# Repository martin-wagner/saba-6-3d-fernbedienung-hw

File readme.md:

### Saba Webradio

Das Saba Webradio erweitert ein Saba Automatic Radio um die folgenden Funktionen:
- W-Lan Webradio
- Steuerung von Automatik und Lautst"arke per Webinterface, MQTT, IR Fernbedienung ...
- Steuerung des Webradio per Radio Automatiktasten

Es kann direkt auf die Anschlussbuchse für die Fernbedienung aufgesteckt werden. Kompatibel sind mind. das Meersburg und Freiburg 6-3D. Am Gerät selbst sind keine Modifikationen notwendig (aber empfehlen). Der Audioausgang des Webradio wird mit dem TA Eingang des Radios verbunden und kann durch Wahl des zugehörigen Eingangs am Radio verwendet werden.

Das Webradio basiert auf dem [ESP32-Radio Projekt von Ed Smallenburg](https://github.com/Edzelf/ESP32-Radio).

[Hardware](https://github.com/martin-wagner/saba-6-3d-fernbedienung-hw)

[Software](https://github.com/martin-wagner/ESP32-Radio)

[Doku](doku/latex/doku.pdf)

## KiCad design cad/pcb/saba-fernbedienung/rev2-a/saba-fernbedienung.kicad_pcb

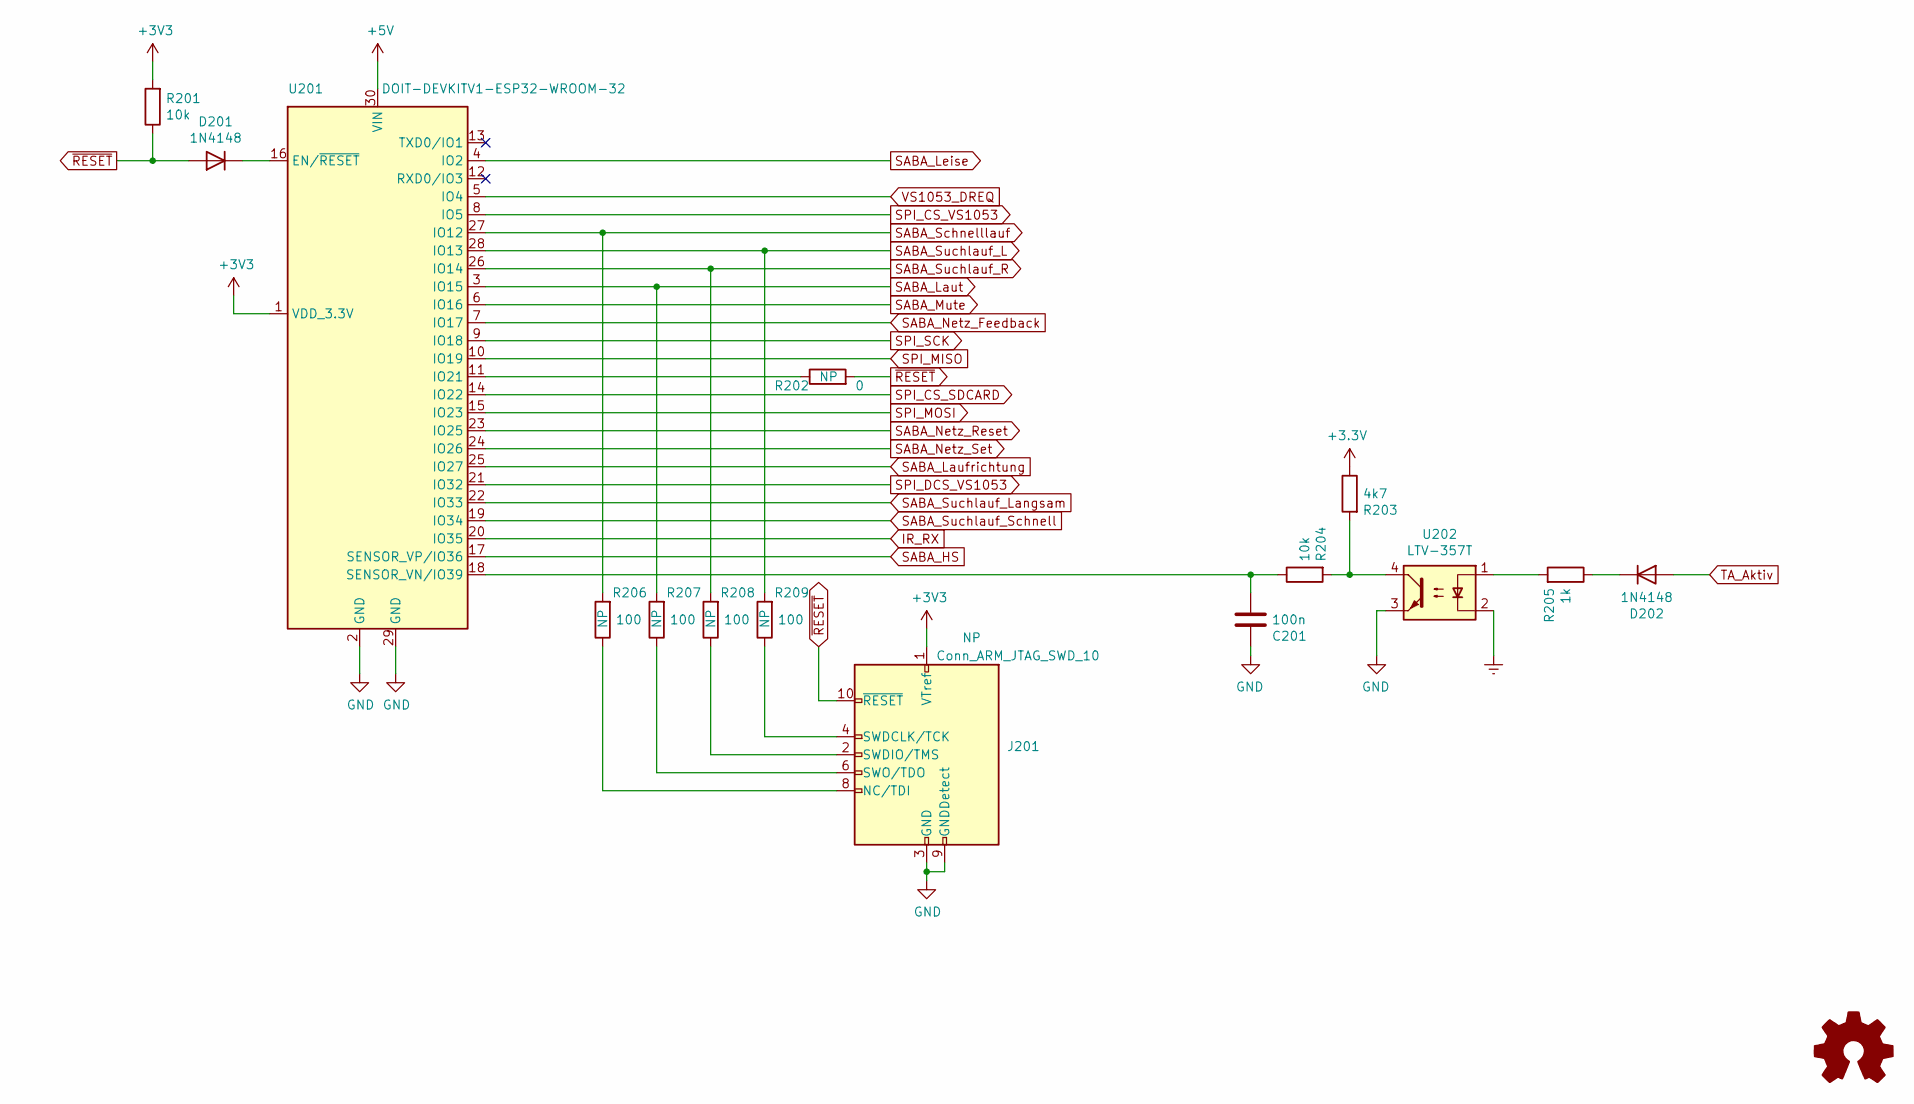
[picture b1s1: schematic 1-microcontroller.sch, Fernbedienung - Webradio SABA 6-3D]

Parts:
C201: 100n; C_0603_1608Metric
D201, D202: 1N4148; D_SOD-323F
J201: Conn_ARM_JTAG_SWD_10; PinHeader_2x05_P1.27mm_Vertical
R201, R204: 10k; R_0603_1608Metric
R202: 0; R_0603_1608Metric
R203: 4k7; R_0603_1608Metric
R205: 1k; R_0603_1608Metric
R206, R207, R208, R209: 100; R_0603_1608Metric
U201: DOIT-DEVKITV1-ESP32-WROOM-32
U202: LTV-357T; SO-4_4.4x3.6mm_P2.54mm

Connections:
+5V: U201.30 (VIN); also elsewhere on the board
Earth: U202.2; also elsewhere on the board
GND: C201.1, J201.3 (GND), J201.5 (GND), J201.9 (GNDDetect), U201.2 (GND), U201.29 (GND), U202.3; also elsewhere on the board
IR_RX: U201.20 (IO35); also elsewhere on the board
unnamed: C201.2, R204.1, U201.18 (SENSOR_VN/IO39)
unnamed: D201.1 (K), U201.16 (EN/~RESET)
unnamed: D202.1 (K), R205.1
unnamed: J201.2 (SWDIO/TMS), R208.1
unnamed: J201.4 (SWDCLK/TCK), R209.1
unnamed: J201.6 (SWO/TDO), R207.1
unnamed: J201.8 (NC/TDI), R206.1
unnamed: R202.1, U201.11 (IO21)
unnamed: R203.2, R204.2, U202.4
unnamed: R205.2, U202.1
SABA_HS: U201.17 (SENSOR_VP/IO36); also elsewhere on the board
SABA_Laufrichtung: U201.25 (IO27); also elsewhere on the board
SABA_Laut: R207.2, U201.3 (IO15); also elsewhere on the board
SABA_Leise: U201.4 (IO2); also elsewhere on the board
SABA_Mute: U201.6 (IO16); also elsewhere on the board
SABA_Netz_Feedback: U201.7 (IO17); also elsewhere on the board
SABA_Netz_Reset: U201.23 (IO25); also elsewhere on the board
SABA_Netz_Set: U201.24 (IO26); also elsewhere on the board
SABA_Schnelllauf: R206.2, U201.27 (IO12); also elsewhere on the board
SABA_Suchlauf_L: R209.2, U201.28 (IO13); also elsewhere on the board
SABA_Suchlauf_Langsam: U201.22 (IO33); also elsewhere on the board
SABA_Suchlauf_R: R208.2, U201.26 (IO14); also elsewhere on the board
SABA_Suchlauf_Schnell: U201.19 (IO34); also elsewhere on the board
SPI_CS_SDCARD: U201.14 (IO22); also elsewhere on the board
SPI_CS_VS1053: U201.8 (IO5); also elsewhere on the board
SPI_DCS_VS1053: U201.21 (IO32); also elsewhere on the board
SPI_MISO: U201.10 (IO19); also elsewhere on the board
SPI_MOSI: U201.15 (IO23); also elsewhere on the board
SPI_SCK: U201.9 (IO18); also elsewhere on the board
TA_Aktiv: D202.2 (A); also elsewhere on the board
VS1053_DREQ: U201.5 (IO4); also elsewhere on the board
~RESET: D201.2 (A), J201.10 (~RESET~), R201.1, R202.2; also elsewhere on the board

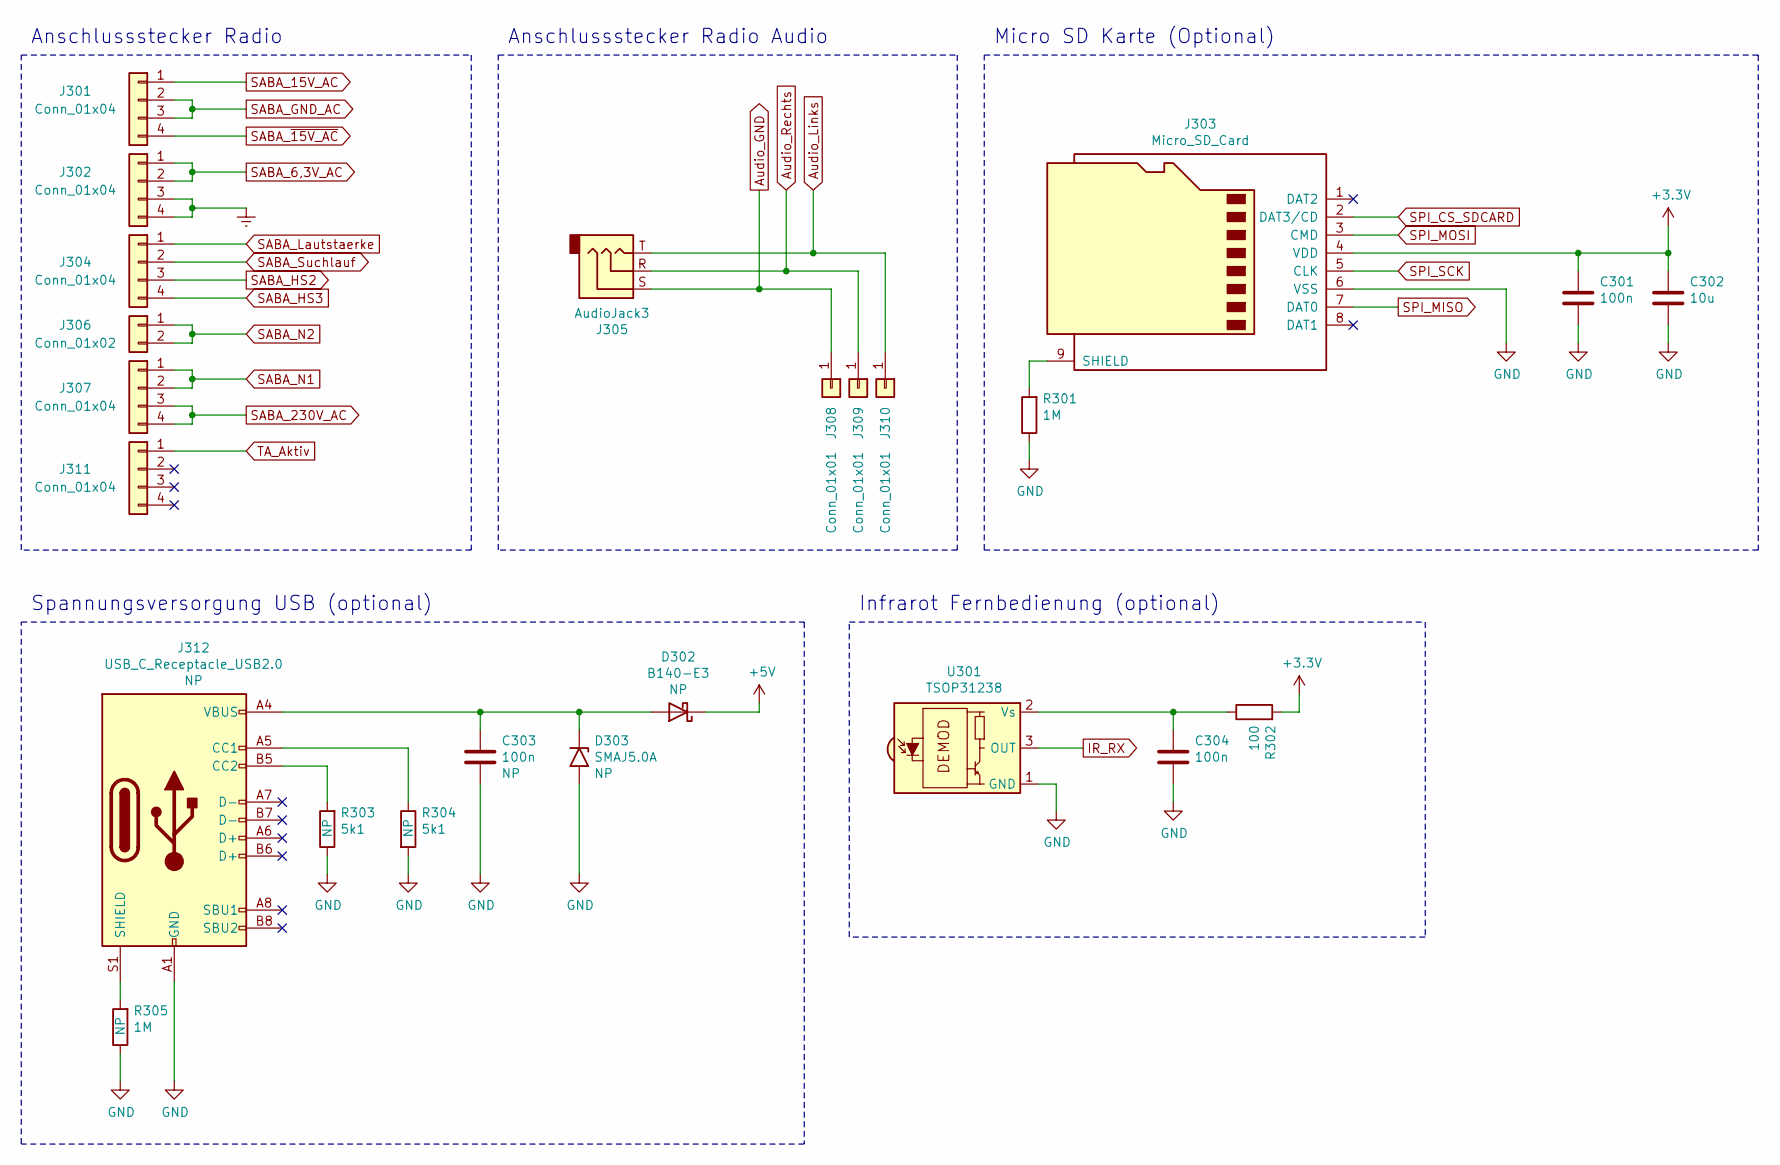
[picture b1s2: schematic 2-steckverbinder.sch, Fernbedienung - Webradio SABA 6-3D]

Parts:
C301, C303, C304: 100n; C_0603_1608Metric
C302: 10u; C_1206_3216Metric
D302: B140-E3; D_SMA
D303: SMAJ5.0A; D_SMA
J301, J302, J304, J307, J311: Conn_01x04; PinHeader_1x04_P2.54mm_Vertical
J303: Micro_SD_Card; microSD_HC_Hirose_DM3AT-SF-PEJM5
J305: AudioJack3; Jack_3.5mm_CUI_SJ-3523-SMT_Horizontal
J306: Conn_01x02; PinHeader_1x02_P2.54mm_Vertical
J308, J309, J310: Conn_01x01; PinHeader_1x01_P2.54mm_Vertical
J312: USB_C_Receptacle_USB2.0; USB_C_Receptacle_HRO_TYPE-C-31-M-12
R301, R305: 1M; R_0603_1608Metric
R302: 100; R_0603_1608Metric
R303, R304: 5k1; R_0603_1608Metric
U301: TSOP31238; Vishay_CAST-3Pin

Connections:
+5V: D302.1 (K); also elsewhere on the board
Audio_GND: J305.S, J308.1; also elsewhere on the board
Audio_Links: J305.T, J310.1; also elsewhere on the board
Audio_Rechts: J305.R, J309.1; also elsewhere on the board
Earth: J302.3, J302.4; also elsewhere on the board
GND: C301.2, C302.2, C303.2, C304.2, D303.2 (A2), J303.6 (VSS), J312.A1 (GND), J312.A12 (GND), J312.B1 (GND), J312.B12 (GND), R301.1, R303.1, R304.2, R305.1, U301.1 (GND); also elsewhere on the board
IR_RX: U301.3 (OUT); also elsewhere on the board
unnamed: C303.1, D302.2 (A), D303.1 (A1), J312.A4 (VBUS), J312.A9 (VBUS), J312.B4 (VBUS), J312.B9 (VBUS)
unnamed: C304.1, R302.1, U301.2 (Vs)
unnamed: J303.9 (SHIELD), R301.2
unnamed: J312.A5 (CC1), R304.1
unnamed: J312.B5 (CC2), R303.2
unnamed: J312.S1 (SHIELD), R305.2
SABA_6,3V_AC: J302.1, J302.2; also elsewhere on the board
SABA_15V_AC: J301.1; also elsewhere on the board
SABA_230V_AC: J307.3, J307.4; also elsewhere on the board
SABA_GND_AC: J301.2, J301.3; also elsewhere on the board
SABA_HS2: J304.3; also elsewhere on the board
SABA_HS3: J304.4; also elsewhere on the board
SABA_Lautstaerke: J304.1; also elsewhere on the board
SABA_N1: J307.1, J307.2; also elsewhere on the board
SABA_N2: J306.1, J306.2; also elsewhere on the board
SABA_Suchlauf: J304.2; also elsewhere on the board
SABA_~15V_AC: J301.4; also elsewhere on the board
SPI_CS_SDCARD: J303.2 (DAT3/CD); also elsewhere on the board
SPI_MISO: J303.7 (DAT0); also elsewhere on the board
SPI_MOSI: J303.3 (CMD); also elsewhere on the board
SPI_SCK: J303.5 (CLK); also elsewhere on the board
TA_Aktiv: J311.1; also elsewhere on the board

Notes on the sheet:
Anschlussstecker Radio
Spannungsversorgung USB (optional)
Micro SD Karte (Optional)
Infrarot Fernbedienung (optional)
Anschlussstecker Radio Audio

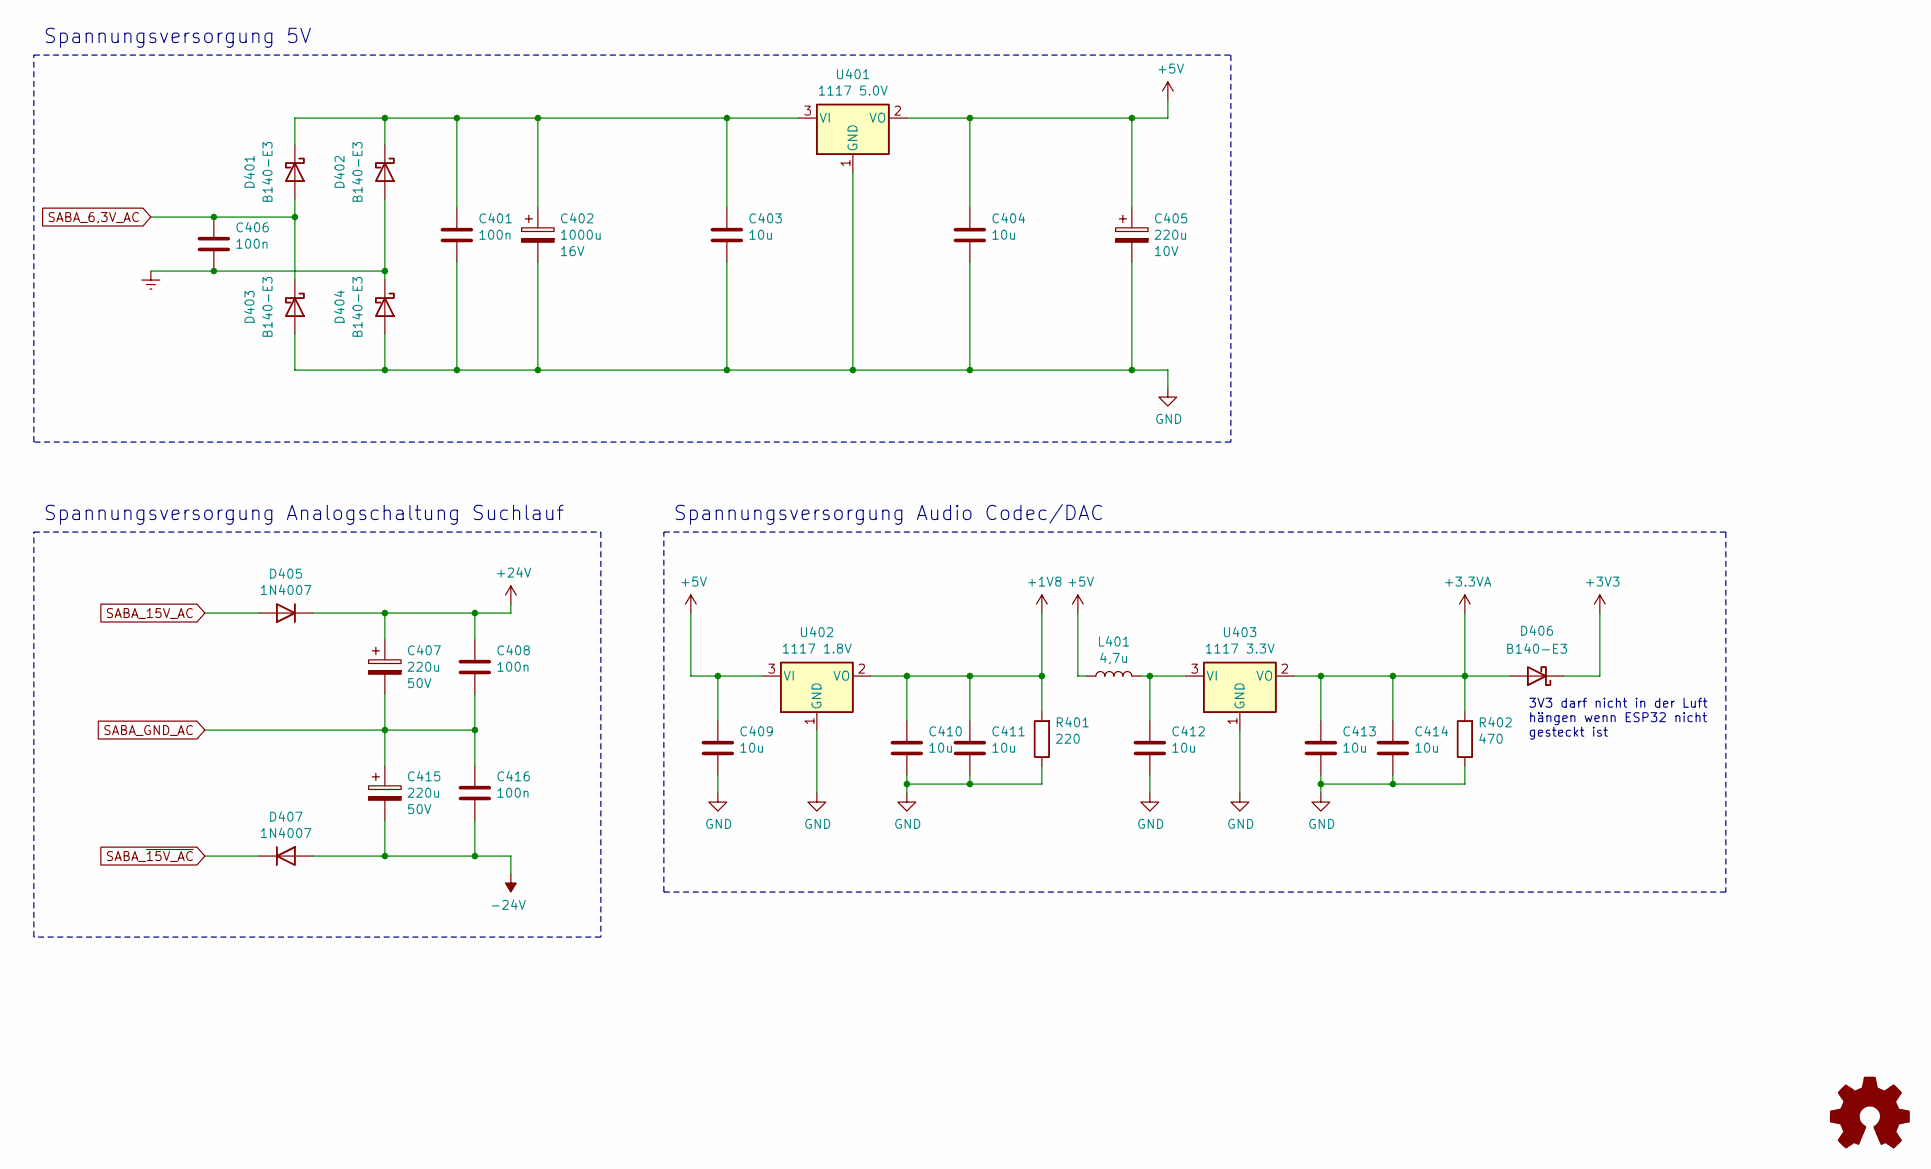
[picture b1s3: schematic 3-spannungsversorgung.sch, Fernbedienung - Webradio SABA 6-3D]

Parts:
C401, C406, C408, C416: 100n; C_0603_1608Metric
C402: 1000u; CP_Radial_D10.0mm_P5.00mm_L20.00mm_liegend; Voltage 16V
C403, C404, C409, C410, C411, C412, C413, C414: 10u; C_1206_3216Metric
C405: 220u; CP_Radial_D10.0mm_P5.00mm_L12.50mm_liegend; Voltage 10V
C407, C415: 220u; CP_Radial_D10.0mm_P5.00mm; Voltage 50V
D401, D402, D403, D404, D406: B140-E3; D_SMA
D405, D407: 1N4007; D_SMA
L401: 4,7u; WE-LQ
R401: 220; R_0603_1608Metric
R402: 470; R_0603_1608Metric
U401: 1117 5.0V; TO-252-3_TabPin2
U402: 1117 1.8V; SOT-223-3_TabPin2
U403: 1117 3.3V; SOT-223-3_TabPin2

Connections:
+1V8: C410.1, C411.1, R401.2, U402.2 (VO); also elsewhere on the board
+3.3VA: C413.1, C414.1, D406.2 (A), R402.2, U403.2 (VO); also elsewhere on the board
+5V: C404.1, C405.1, C409.1, L401.1, U401.2 (VO), U402.3 (VI); also elsewhere on the board
+24V: C407.1, C408.1, D405.1 (K); also elsewhere on the board
-24V: C415.2, C416.2, D407.2 (A); also elsewhere on the board
Earth: C406.2, D402.2 (A), D404.1 (K); also elsewhere on the board
GND: C401.2, C402.2, C403.2, C404.2, C405.2, C409.2, C410.2, C411.2, C412.2, C413.2, C414.2, D403.2 (A), D404.2 (A), R401.1, R402.1, U401.1 (GND), U402.1 (GND), U403.1 (GND); also elsewhere on the board
unnamed: C401.1, C402.1, C403.1, D401.1 (K), D402.1 (K), U401.3 (VI)
unnamed: C412.1, L401.2, U403.3 (VI)
SABA_6,3V_AC: C406.1, D401.2 (A), D403.1 (K); also elsewhere on the board
SABA_15V_AC: D405.2 (A); also elsewhere on the board
SABA_GND_AC: C407.2, C408.2, C415.1, C416.1; also elsewhere on the board
SABA_~15V_AC: D407.1 (K); also elsewhere on the board

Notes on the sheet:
Spannungsversorgung 5V
Spannungsversorgung Analogschaltung Suchlauf
Spannungsversorgung Audio Codec/DAC
3V3 darf nicht in der Luft hängen wenn ESP32 nicht gesteckt ist

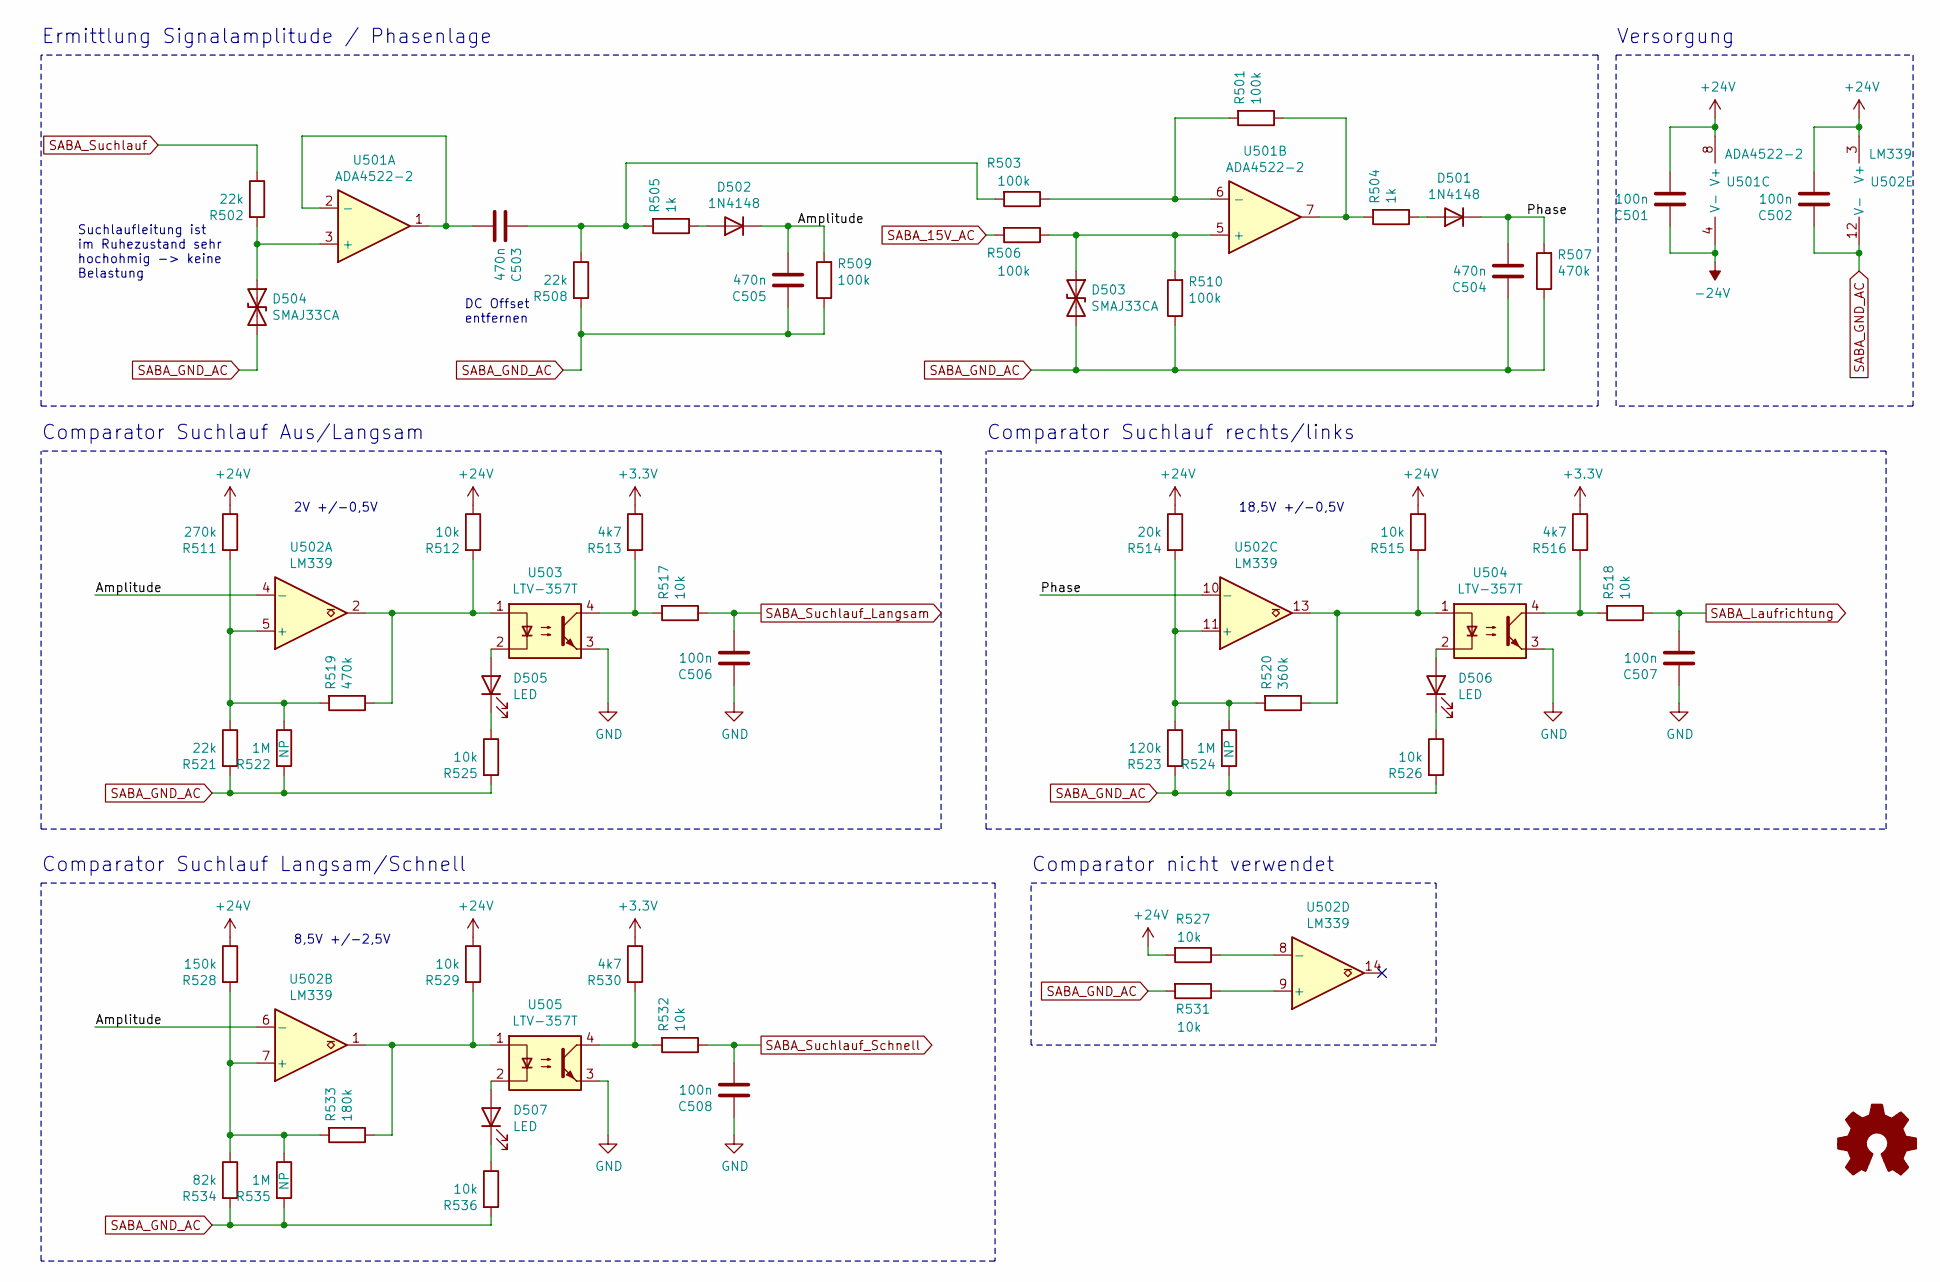
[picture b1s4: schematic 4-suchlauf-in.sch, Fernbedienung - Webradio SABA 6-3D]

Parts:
C501, C502, C506, C507, C508: 100n; C_0603_1608Metric
C503, C504, C505: 470n; C_0805_2012Metric
D501, D502: 1N4148; D_SOD-323F
D503, D504: SMAJ33CA; D_SMA
D505, D506, D507: LED; LED_0805_2012Metric
R501, R503, R506, R509, R510: 100k; R_0603_1608Metric
R502, R508, R521: 22k; R_0603_1608Metric
R504, R505: 1k; R_0603_1608Metric
R507, R519: 470k; R_0603_1608Metric
R511: 270k; R_0603_1608Metric
R512, R515, R517, R518, R525, R526, R527, R529, R531, R532, R536: 10k; R_0603_1608Metric
R513, R516, R530: 4k7; R_0603_1608Metric
R514: 20k; R_0603_1608Metric
R520: 360k; R_0603_1608Metric
R522, R524, R535: 1M; R_0603_1608Metric
R523: 120k; R_0603_1608Metric
R528: 150k; R_0603_1608Metric
R533: 180k; R_0603_1608Metric
R534: 82k; R_0603_1608Metric
U501: ADA4522-2; SOIC-8_3.9x4.9mm_P1.27mm
U502: LM339; SOIC-14_3.9x8.7mm_P1.27mm
U503, U504, U505: LTV-357T; SO-4_4.4x3.6mm_P2.54mm

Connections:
+24V: C501.2, C502.2, R511.1, R512.1, R514.1, R515.1, R527.2, R528.1, R529.1, U501.8 (V+), U502.3 (V+); also elsewhere on the board
-24V: C501.1, U501.4 (V-); also elsewhere on the board
/Suchlauf Messung/Amplitude: C505.2, D502.1 (K), R509.2, U502.4 (-), U502.6 (-)
/Suchlauf Messung/Phase: C504.2, D501.1 (K), R507.2, U502.10 (-)
GND: C506.1, C507.1, C508.1, U503.3, U504.3, U505.3; also elsewhere on the board
unnamed: C503.1, R503.2, R505.2, R508.1
unnamed: C503.2, U501.1, U501.2 (-)
unnamed: D501.2 (A), R504.1
unnamed: D502.2 (A), R505.1
unnamed: D503.1 (A1), R506.1, R510.2, U501.5 (+)
unnamed: D504.1 (A1), R502.2, U501.3 (+)
unnamed: D505.1 (K), R525.1
unnamed: D505.2 (A), U503.2
unnamed: D506.1 (K), R526.1
unnamed: D506.2 (A), U504.2
unnamed: D507.1 (K), R536.1
unnamed: D507.2 (A), U505.2
unnamed: R501.1, R504.2, U501.7
unnamed: R501.2, R503.1, U501.6 (-)
unnamed: R511.2, R519.2, R521.1, R522.1, U502.5 (+)
unnamed: R512.2, R519.1, U502.2, U503.1
unnamed: R513.2, R517.2, U503.4
unnamed: R514.2, R520.2, R523.1, R524.1, U502.11 (+)
unnamed: R515.2, R520.1, U502.13, U504.1
unnamed: R516.2, R518.2, U504.4
unnamed: R527.1, U502.8 (-)
unnamed: R528.2, R533.2, R534.1, R535.1, U502.7 (+)
unnamed: R529.2, R533.1, U502.1, U505.1
unnamed: R530.2, R532.2, U505.4
unnamed: R531.1, U502.9 (+)
SABA_15V_AC: R506.2; also elsewhere on the board
SABA_GND_AC: C502.1, C504.1, C505.1, D503.2 (A2), D504.2 (A2), R507.1, R508.2, R509.1, R510.1, R521.2, R522.2, R523.2, R524.2, R525.2, R526.2, R531.2, R534.2, R535.2, R536.2, U502.12 (V-); also elsewhere on the board
SABA_Laufrichtung: C507.2, R518.1; also elsewhere on the board
SABA_Suchlauf: R502.1; also elsewhere on the board
SABA_Suchlauf_Langsam: C506.2, R517.1; also elsewhere on the board
SABA_Suchlauf_Schnell: C508.2, R532.1; also elsewhere on the board

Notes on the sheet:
Ermittlung Signalamplitude / Phasenlage
Suchlaufleitung ist im Ruhezustand sehr hochohmig -> keine Belastung
DC Offset entfernen
2V +/-0,5V
Comparator Suchlauf Aus/Langsam
Comparator Suchlauf Langsam/Schnell
8,5V +/-2,5V
18,5V +/-0,5V
Comparator Suchlauf rechts/links
Comparator nicht verwendet
Versorgung

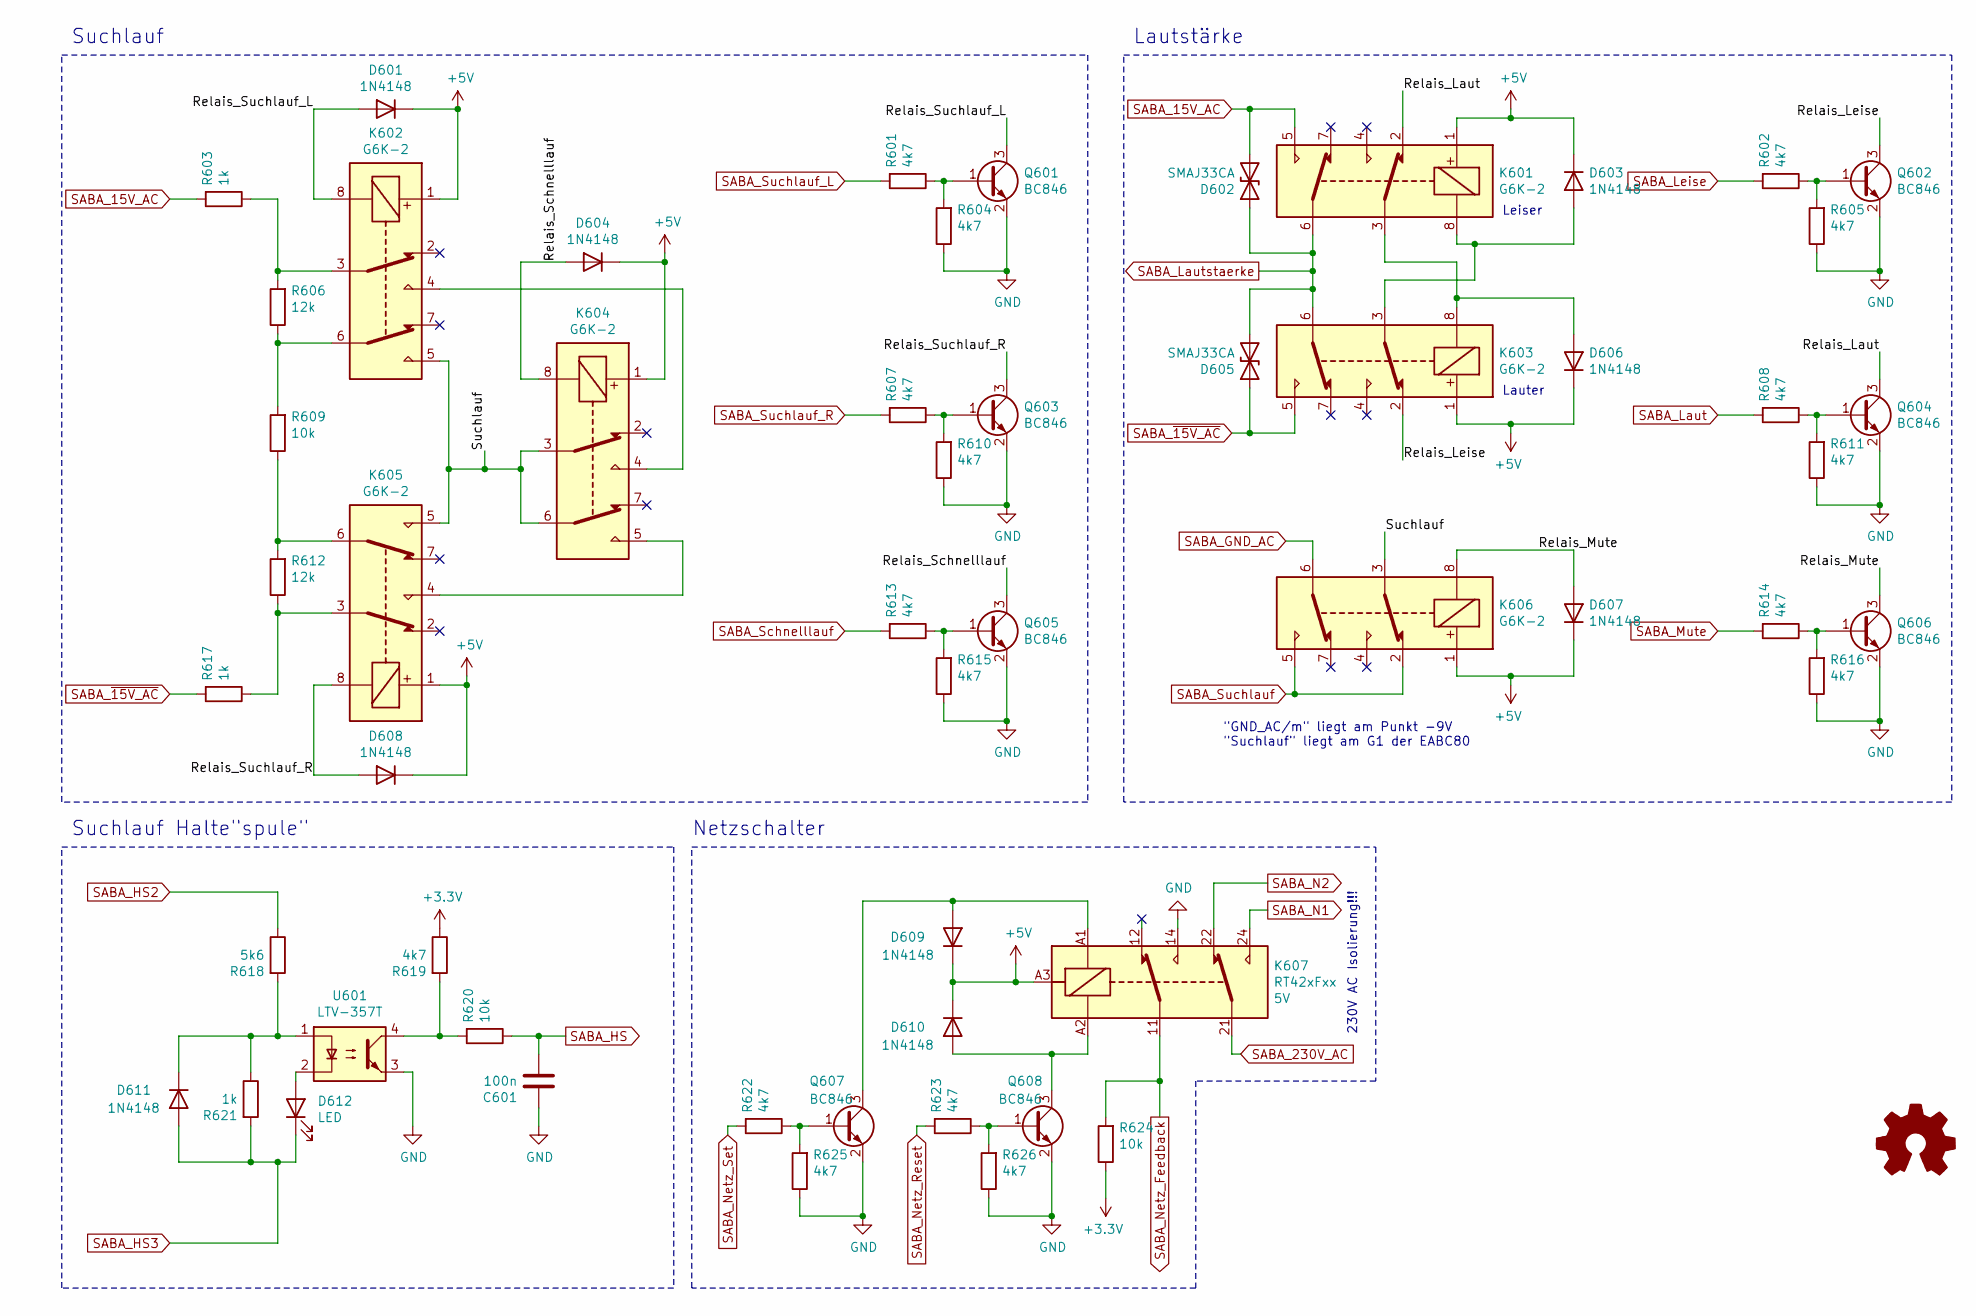
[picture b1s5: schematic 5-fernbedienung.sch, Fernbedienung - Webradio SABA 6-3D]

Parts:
C601: 100n; C_0603_1608Metric
D601, D603, D604, D606, D607, D608, D609, D610, D611: 1N4148; D_SOD-323F
D602, D605: SMAJ33CA; D_SMA
D612: LED; LED_0805_2012Metric
K601, K602, K603, K604, K605, K606: G6K-2; Relay_DPDT_Omron_G6K-2P
K607: RT42xFxx; Relay_DPDT_Schrack-RT2-FormC-Dual-Coil_RM5mm; Coil Voltage 5V
Q601, Q602, Q603, Q604, Q605, Q606, Q607, Q608: BC846; SOT-23
R601, R602, R604, R605, R607, R608, R610, R611, R613, R614, R615, R616, R619, R622, R623, R625, R626: 4k7; R_0603_1608Metric
R603, R617: 1k; R_Axial_DIN0207_L6.3mm_D2.5mm_P7.62mm_Horizontal
R606, R612: 12k; R_0603_1608Metric
R609, R620, R624: 10k; R_0603_1608Metric
R618: 5k6; R_Axial_DIN0207_L6.3mm_D2.5mm_P7.62mm_Horizontal
R621: 1k; R_0603_1608Metric
U601: LTV-357T; SO-4_4.4x3.6mm_P2.54mm

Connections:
+5V: D601.1 (K), D603.1 (K), D604.1 (K), D606.1 (K), D607.1 (K), D608.1 (K), D609.1 (K), D610.1 (K), K601.1, K602.1, K603.1, K604.1, K605.1, K606.1, K607.A3; also elsewhere on the board
/Fernbedienung/Relais_Laut: K601.2, Q604.3 (C)
/Fernbedienung/Relais_Leise: K603.2, Q602.3 (C)
/Fernbedienung/Relais_Mute: D607.2 (A), K606.8, Q606.3 (C)
/Fernbedienung/Relais_Schnelllauf: D604.2 (A), K604.8, Q605.3 (C)
/Fernbedienung/Relais_Suchlauf_L: D601.2 (A), K602.8, Q601.3 (C)
/Fernbedienung/Relais_Suchlauf_R: D608.2 (A), K605.8, Q603.3 (C)
/Fernbedienung/Suchlauf: K602.5, K604.3, K604.6, K605.5, K606.3
GND: C601.1, K607.14, Q601.2 (E), Q602.2 (E), Q603.2 (E), Q604.2 (E), Q605.2 (E), Q606.2 (E), Q607.2 (E), Q608.2 (E), R604.1, R605.1, R610.1, R611.1, R615.1, R616.1, R625.1, R626.1, U601.3; also elsewhere on the board
unnamed: D603.2 (A), K601.8, K603.3
unnamed: D606.2 (A), K601.3, K603.8
unnamed: D609.2 (A), K607.A1, Q607.3 (C)
unnamed: D610.2 (A), K607.A2, Q608.3 (C)
unnamed: D611.1 (K), R618.2, R621.1, U601.1
unnamed: D612.2 (A), U601.2
unnamed: K602.3, R603.1, R606.2
unnamed: K602.4, K604.4
unnamed: K602.6, R606.1, R609.2
unnamed: K604.5, K605.4
unnamed: K605.3, R612.1, R617.1
unnamed: K605.6, R609.1, R612.2
unnamed: Q601.1 (B), R601.1, R604.2
unnamed: Q602.1 (B), R602.1, R605.2
unnamed: Q603.1 (B), R607.1, R610.2
unnamed: Q604.1 (B), R608.1, R611.2
unnamed: Q605.1 (B), R613.1, R615.2
unnamed: Q606.1 (B), R614.1, R616.2
unnamed: Q607.1 (B), R622.1, R625.2
unnamed: Q608.1 (B), R623.1, R626.2
unnamed: R619.2, R620.2, U601.4
SABA_15V_AC: D602.2 (A2), K601.5, R603.2; also elsewhere on the board
SABA_230V_AC: K607.21; also elsewhere on the board
SABA_GND_AC: K606.6; also elsewhere on the board
SABA_HS: C601.2, R620.1; also elsewhere on the board
SABA_HS2: R618.1; also elsewhere on the board
SABA_HS3: D611.2 (A), D612.1 (K), R621.2; also elsewhere on the board
SABA_Laut: R608.2; also elsewhere on the board
SABA_Lautstaerke: D602.1 (A1), D605.2 (A2), K601.6, K603.6; also elsewhere on the board
SABA_Leise: R602.2; also elsewhere on the board
SABA_Mute: R614.2; also elsewhere on the board
SABA_N1: K607.24; also elsewhere on the board
SABA_N2: K607.22; also elsewhere on the board
SABA_Netz_Feedback: K607.11, R624.2; also elsewhere on the board
SABA_Netz_Reset: R623.2; also elsewhere on the board
SABA_Netz_Set: R622.2; also elsewhere on the board
SABA_Schnelllauf: R613.2; also elsewhere on the board
SABA_Suchlauf: K606.2, K606.5; also elsewhere on the board
SABA_Suchlauf_L: R601.2; also elsewhere on the board
SABA_Suchlauf_R: R607.2; also elsewhere on the board
SABA_~15V_AC: D605.1 (A1), K603.5, R617.2; also elsewhere on the board

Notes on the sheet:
Suchlauf
Suchlauf Halte"spule"
"GND_AC/m" liegt am Punkt -9V "Suchlauf" liegt am G1 der EABC80
Lautstärke
Lauter
Leiser
230V AC Isolierung!!!
Netzschalter

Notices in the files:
cad/pcb/saba-fernbedienung-anschlussstecker/rev1-a/saba-fernbedienung-anschlussstecker.sch:
Lizenz: CERN-OHL-W (OHL v2)
